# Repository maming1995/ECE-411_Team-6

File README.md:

# ECE-411_Team-6
ECE 411 Practicum Project of team 6

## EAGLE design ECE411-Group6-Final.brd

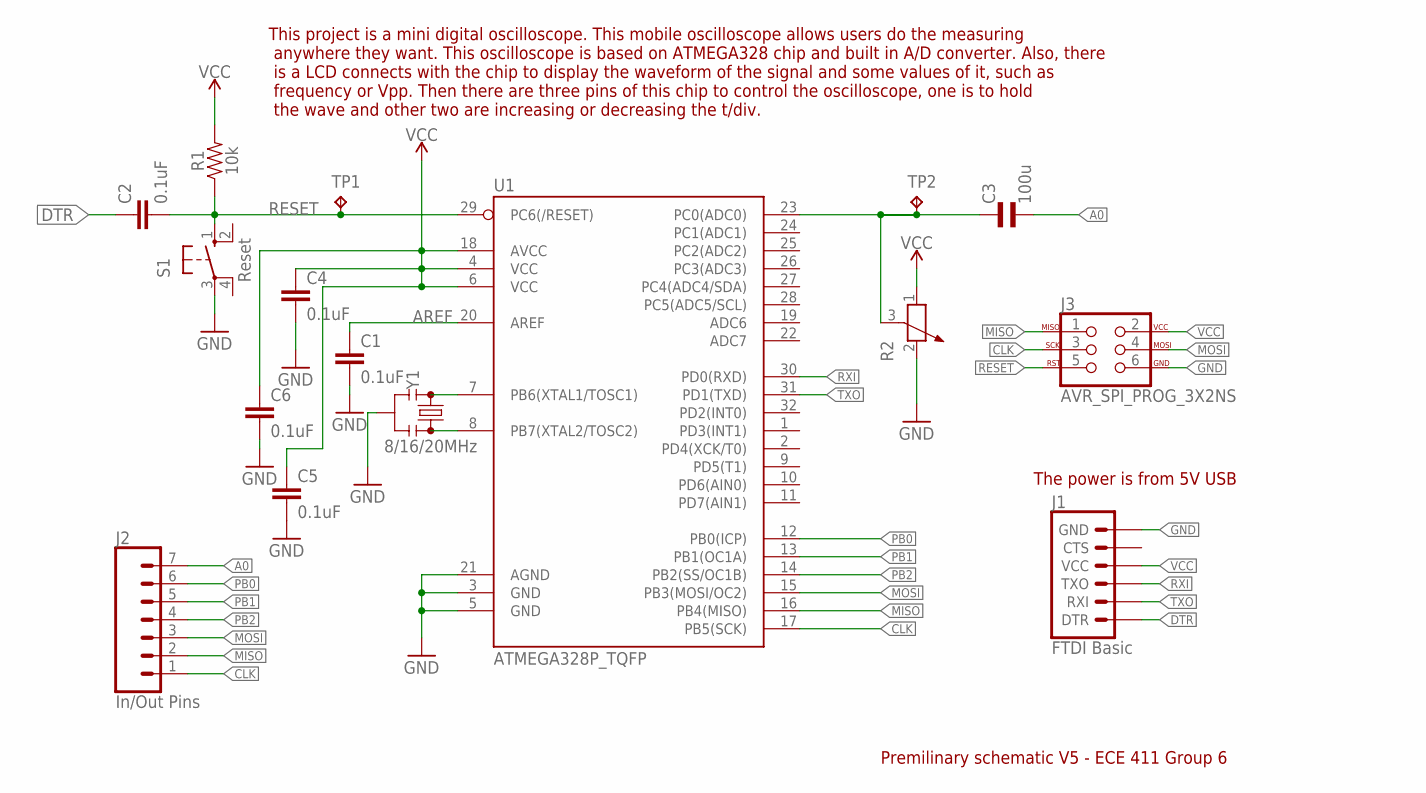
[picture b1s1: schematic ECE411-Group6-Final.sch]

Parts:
C1, C2, C4, C5, C6: 0.1uF; 0603
C3: 100u; EU25-10
J1: FTDI Basic; 1X06
J2: In/Out Pins; 1X07
J3: AVR_SPI_PROG_3X2NS; 2X3-NS
R1: 10k; 0603
R2: POTENTIOMETER_PT-10; PT-10
S1: Reset; B3F-10XX
TP1, TP2: TPB1,27; B1,27
U1: ATMEGA328P_TQFP; TQFP32-08
Y1: 8/16/20MHz; RESONATOR-SMD-3.2X1.3

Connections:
A0: C3.2, J2.7
AREF: C1.1, U1.20 (AREF)
CLK: J2.1, J3.3, U1.17 (PB5(SCK))
DTR: C2.1, J1.1 (DTR)
GND: C1.2, C4.2, C5.2, C6.2, J1.6 (GND), J3.6, R2.2, S1.3, U1.3 (GND), U1.5 (GND), U1.21 (AGND), Y1.2
MISO: J2.2, J3.1, U1.16 (PB4(MISO))
MOSI: J2.3, J3.4, U1.15 (PB3(MOSI/OC2))
unnamed: U1.7 (PB6(XTAL1/TOSC1)), Y1.1
unnamed: U1.8 (PB7(XTAL2/TOSC2)), Y1.3
unnamed: C3.1, R2.3, TP2.TP, U1.23 (PC0(ADC0))
PB0: J2.6, U1.12 (PB0(ICP))
PB1: J2.5, U1.13 (PB1(OC1A))
PB2: J2.4, U1.14 (PB2(SS/OC1B))
RESET: C2.2, J3.5, R1.1, S1.1 (S), TP1.TP, U1.29 (PC6(/RESET))
RXI: J1.3 (TXO), U1.30 (PD0(RXD))
TXO: J1.2 (RXI), U1.31 (PD1(TXD))
VCC: C4.1, C5.1, C6.1, J1.4 (VCC), J3.2, R1.2, R2.1, U1.4 (VCC), U1.6 (VCC), U1.18 (AVCC)

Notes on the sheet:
Premilinary schematic V5 - ECE 411 Group 6
The power is from 5V USB
This project is a mini digital oscilloscope. This mobile oscilloscope allows users do the measuring anywhere they want. This oscilloscope is based on ATMEGA328 chip and built in A/D converter. Also, there is a LCD connects with the chip to display the waveform of the signal and some values of it, s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

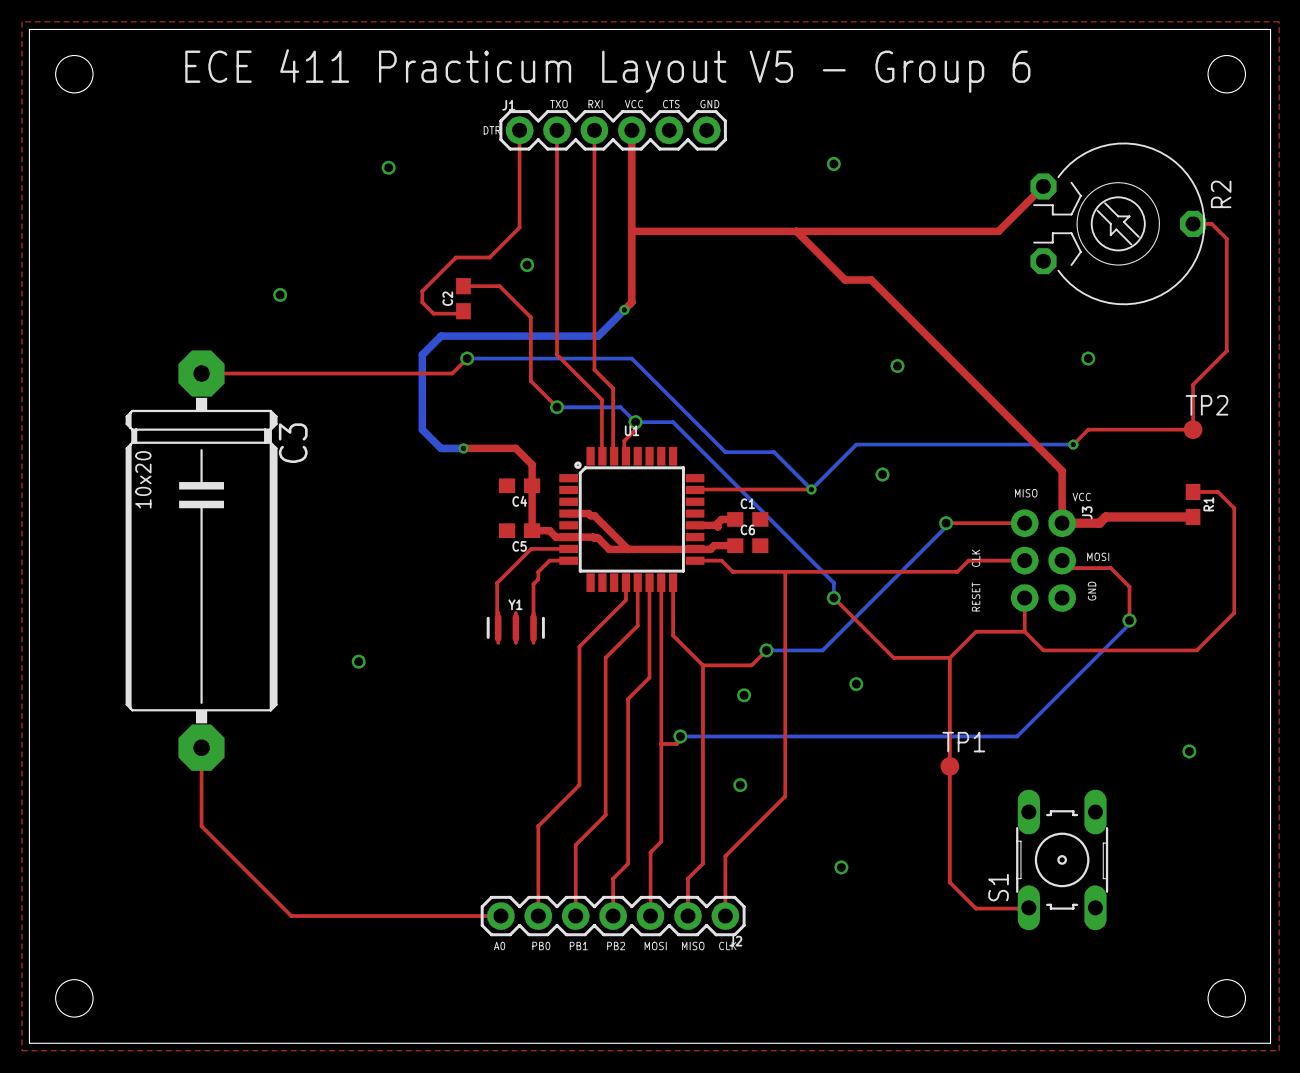
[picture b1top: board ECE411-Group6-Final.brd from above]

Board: 2 copper layers, 84.3 x 68.8 mm, 16 parts (0 on the bottom side), 17 nets.

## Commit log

2017-10-16 Add files via upload
    Hey all,
    So, this 'works.' I have not really tested it out yet. I plan on fixing up the code to make it look nicer, as well as putting in some descriptive comments so you all know what I am doing. I also plan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
    Anyway,
    please see if you can run it and tell me if you notice any bugs.
2017-10-17 Add files via upload
    Hey guys.
    I got the recursion thing working now.
2017-11-09 Create Layout
2017-11-09 Add files via upload
    This is the layout file for ECE411-Group6-V1 schematic
2017-11-12 Add files via upload
    Fixed the pushbutton. Upload the new vision of schematic and layout
2017-12-02 test case

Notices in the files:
parts and their libraries:
SparkFun-Capacitors: Licensing: Creative Commons ShareAlike 4.0 International - https://creativecommons.org/licenses/by-sa/4.0
